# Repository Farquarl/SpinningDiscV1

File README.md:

# SpinningDiscV1
Documentation for the SpinningDisc ZMNH germany.

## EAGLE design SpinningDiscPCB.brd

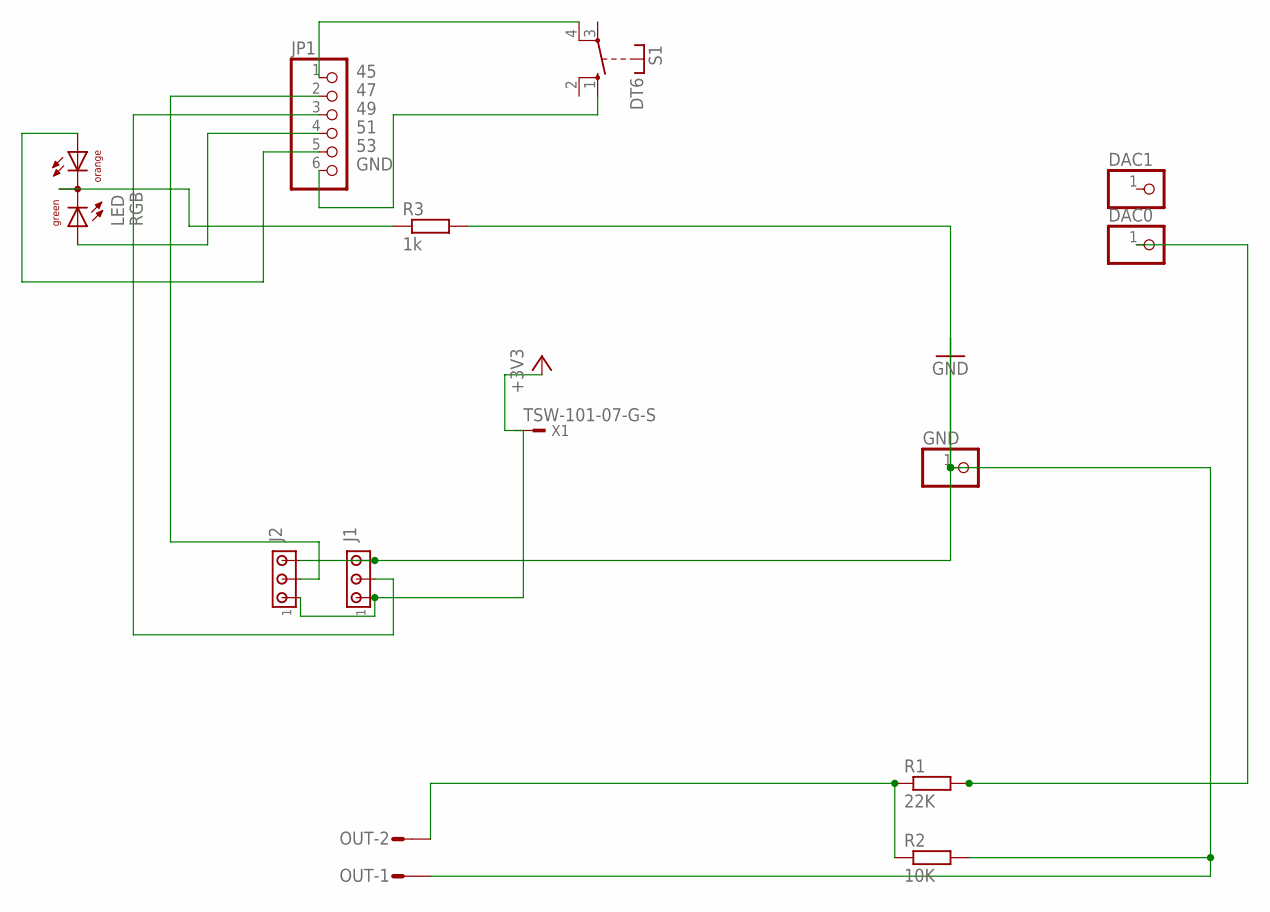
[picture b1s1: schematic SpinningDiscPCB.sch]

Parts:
DAC0, DAC1: PINHD-1X1; 1X01
GND: PINHD-1X1; 1X01
J1, J2: MTA03-100; 10X03MTA
JP1: PINHD-1X6; 1X06
LED: RGB; TLUV5300
OUT: L02P
R1: 22K; 0207/10
R2: 10K; 0207/10
R3: 1k; 0207/10
S1: DT6
X1: TSW-101-07-G-S; TSW-101-XX-G-S

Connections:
45: JP1.1, S1.4
47: J2.2, JP1.2
49: J1.2, JP1.3
51: JP1.4, LED.AG
53: JP1.5, LED.AO
+3V3: J1.1, J2.1, X1.1
GND: GND.1, J1.3, J2.3, LED.CC, OUT.1, R2.2, R3.1, R3.2
unnamed: JP1.6, S1.1 (S)
unnamed: DAC0.1, R1.2
unnamed: OUT.2, R1.1, R2.1

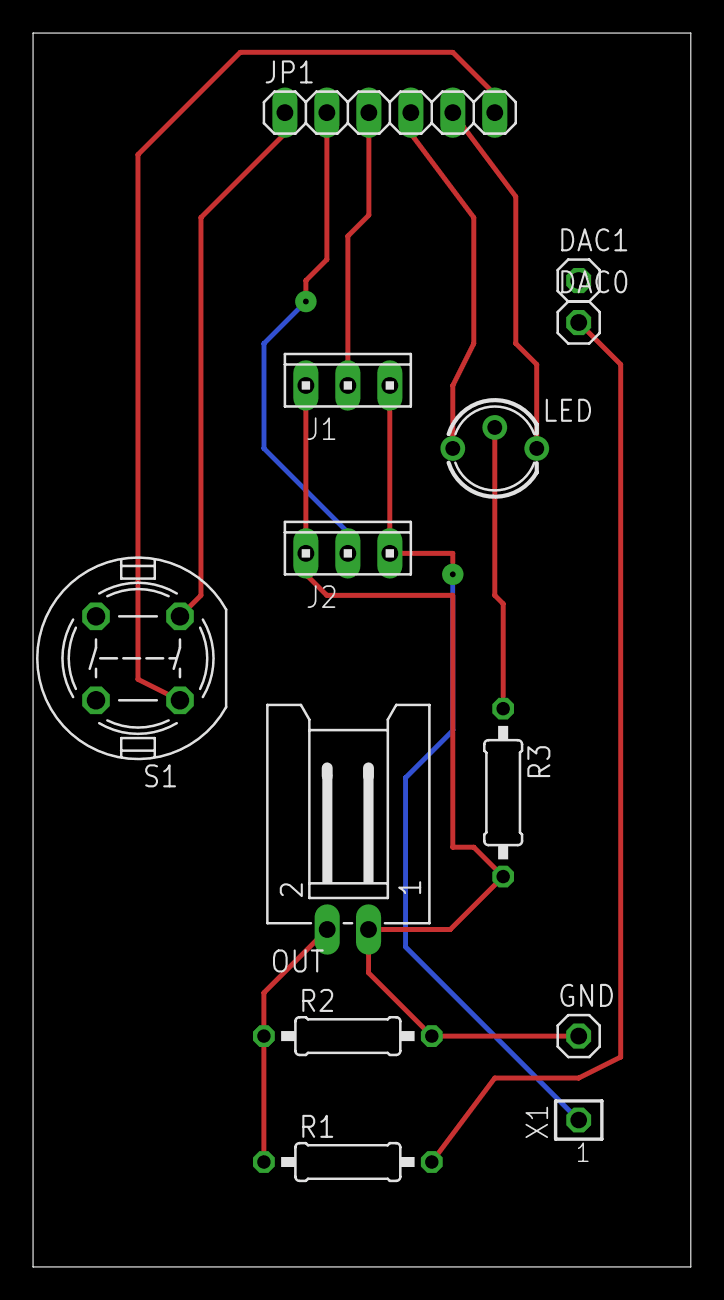
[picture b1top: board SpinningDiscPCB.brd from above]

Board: 2 copper layers, 39.8 x 74.7 mm, 13 parts (0 on the bottom side), 10 nets.
